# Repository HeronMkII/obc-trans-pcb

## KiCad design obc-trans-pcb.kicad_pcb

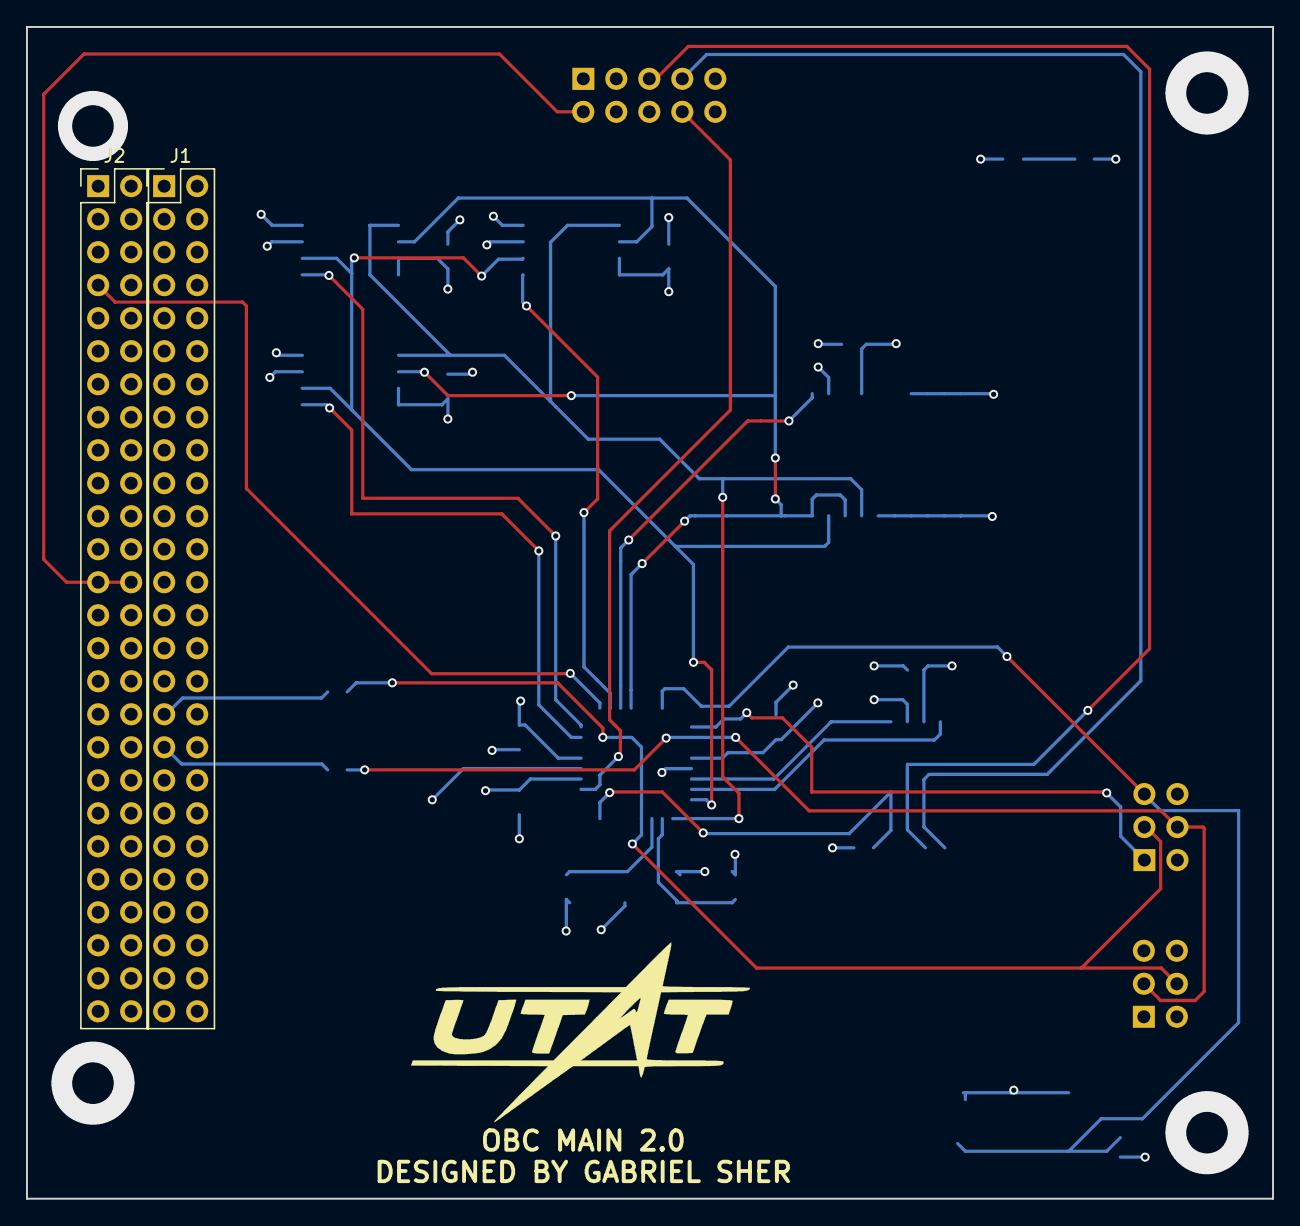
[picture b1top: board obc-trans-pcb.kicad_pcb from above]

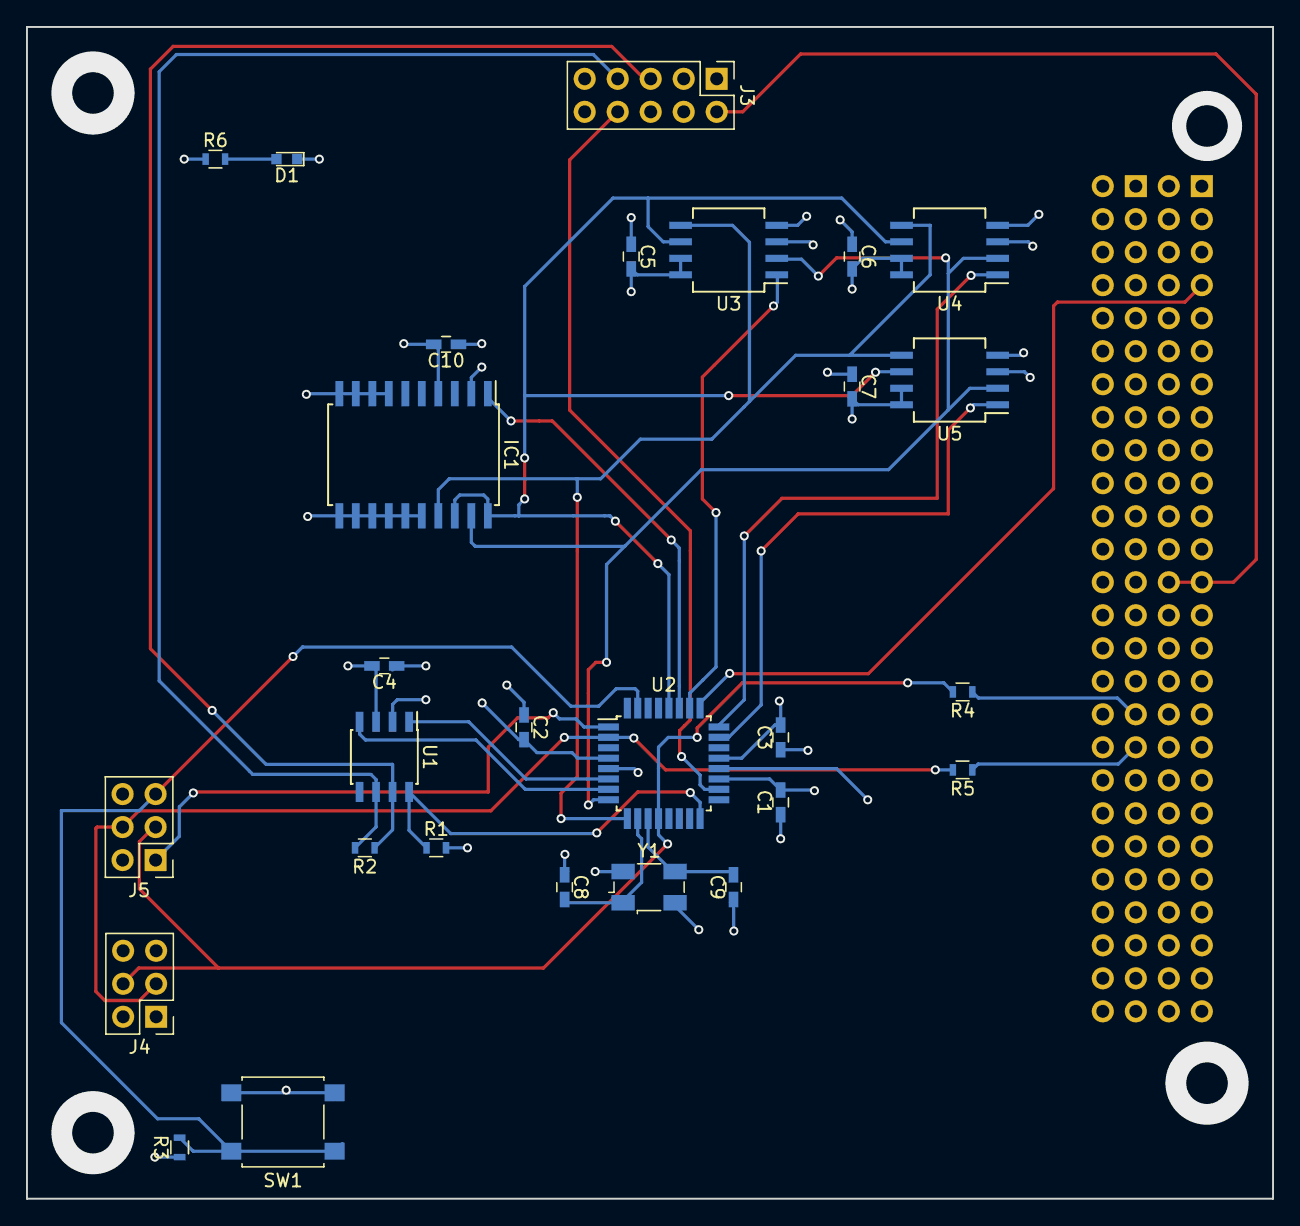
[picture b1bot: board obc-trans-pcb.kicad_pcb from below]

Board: 4 copper layers, 95.9 x 90.2 mm, 30 parts (28 on the bottom side), 26 nets.

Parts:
C1, C2, C3, C4, C5, C6, C7, C10: 100nF; C_0603_HandSoldering
C8, C9: 22pF; C_0603_HandSoldering
D1: PWR_LED; LED_0603
IC1: DS3234; SOIC-20W_7.5x12.8mm_Pitch1.27mm
J1: H1; Pin_Header_Straight_2x26_Pitch2.54mm
J2: H2; Pin_Header_Straight_2x26_Pitch2.54mm
J3: H_EPS; Pin_Header_Straight_2x05_Pitch2.54mm
J4: DEBUGGING PORT; Pin_Header_Straight_2x03_Pitch2.54mm
J5: PROGRAMMING PORT; Pin_Header_Straight_2x03_Pitch2.54mm
R1: 1K; R_0603
R2, R6: 120R; R_0603
R3: 10K; R_0603
R4, R5: 0R; R_0603
SW1: SW_RST; SW_SPST_B3S-1000
U1: SN65HVD230; SOIC-8_3.9x4.9mm_Pitch1.27mm
U2: ATMEGA32M1-MU; TQFP-32_7x7mm_Pitch0.8mm
U3, U4, U5: SST25VF016B; SO-8_5.3x6.2mm_Pitch1.27mm
Y1: 8 MHz; Crystal_SMD_Abracon_ABM3B-4pin_5.0x3.2mm

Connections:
+3V3: C1.2, C2.2, C3.2, C4.2, C5.2, C6.2, C7.2, C10.2, IC1.4, J2.27, J2.28, J3.1, J4.1, J4.2, J5.2, R3.1, R6.1, U1.3, U2.4, U2.19, U2.21, U3.3, U3.7, U3.8, U4.3, U4.7, U4.8, U5.3, U5.7, U5.8
+5V: J2.25, J2.26, J3.2
/CANH: J3.5, R2.1, U1.7
/CANL: J3.7, R2.2, U1.6
/CAN_LPWR: R1.1, U1.8, U2.16
/CAN_RX: U1.4, U2.7
/CAN_TX: U1.1, U2.6
/COM_RXD: J1.33, R4.1
/COM_TXD: J1.35, R5.1
/CS_MEM1: U2.26, U3.1
/CS_MEM2: U2.24, U4.1
/CS_MEM3: U2.23, U5.1
/CS_RTC: IC1.1, U2.27
/EN_UHF: J2.7, U2.25
/EPS_RST: J3.8, U2.18
/MISO: IC1.19, U2.8, U3.2, U4.2, U5.2
/MISO_A: J5.1, U2.1
/MOSI: IC1.17, U2.9, U3.5, U4.5, U5.5
/MOSI_A: J4.3, J5.4, R5.2, U2.2
/RST: J5.5, R3.2, SW1.1, U2.31
/SCK: IC1.18, IC1.20, U2.28, U3.6, U4.6, U5.6
/SCK_A: J4.4, J5.3, R4.2, U2.12
GND: C1.1, C2.1, C3.1, C4.1, C5.1, C6.1, C7.1, C8.1, C9.1, C10.1, D1.1, IC1.2, IC1.7, IC1.8, IC1.9, IC1.10, IC1.11, IC1.12, IC1.13, IC1.14, IC1.15, IC1.16, J2.29, J2.30, J2.31, J2.32, J3.9, J3.10, J4.5, J4.6, J5.6, R1.2, SW1.2, U1.2, U2.5, U2.20, U3.4, U4.4, U5.4, Y1.2, Y1.4
unnamed: C8.2, U2.10, Y1.1
unnamed: C9.2, U2.11, Y1.3
unnamed: D1.2, R6.2

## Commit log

2018-02-01 added components to .sch
    missing nets and connectors to other boards
2018-02-02 some changes
    added some nets. current remaining
    schematic needs:
    * add connectors
    * create & add footprint for transceiver
    * add power nets for MCU
    * confirm all nets are in place
2018-02-03 basically finished schematic :(
2018-02-03 actually done sch
2018-02-03 actually done fr
2018-02-05 v1 layout, without GND & 3V3 planes
    Everything should be connected. Sorry it looks uggles :(
2018-02-05 finished layout
2018-02-07 corrected some pads, caps, & vias
    fixed vias too close together, corrected via clearance, fixed some caps wired incorrectly (I think), renamed inner layers for clarity. Also connected a pad I missed
2018-02-07 project file updated?
2018-02-10 fixed corner locations, header location, pours
2018-02-17 vias smaller
2018-02-17 removed needless traces
2018-02-17 text added
2018-02-17 some change its making me push, to be undone
2018-02-17 Revert "fixed corner locations, header location, pours"
    This reverts commit 1e2a4b22dfbf382ebc9556c6fbeeac2429f8bf98.
2018-02-17 Revert "Revert "fixed corner locations, header location, pours""
    This reverts commit 6816b7f7674ef2cac55d919e79431994bfc36912.
2018-02-17 Revert "some change its making me push, to be undone"
    This reverts commit 0c28c69a38c24636102bb3d43f2e0016dafd29cc.
2018-02-17 Revert "text added"
    This reverts commit e1df546076587439d09c56251eebff1379ce6698.
2018-02-17 Revert "removed needless traces"
    This reverts commit 13567706eda5130220792ebe949a07ef88a05d37.
2018-02-17 Revert "vias smaller"
    This reverts commit cac4902e6433adb27f0d020128540fc5646aa025.
2018-02-17 .8 mm vias + logo
2018-02-17 finished 1.2 holes and drawings
2018-02-17 reverted to 0.8 holes
2018-02-18 Housekeeping changes
2018-03-04 added .grb files and removed excess traces
